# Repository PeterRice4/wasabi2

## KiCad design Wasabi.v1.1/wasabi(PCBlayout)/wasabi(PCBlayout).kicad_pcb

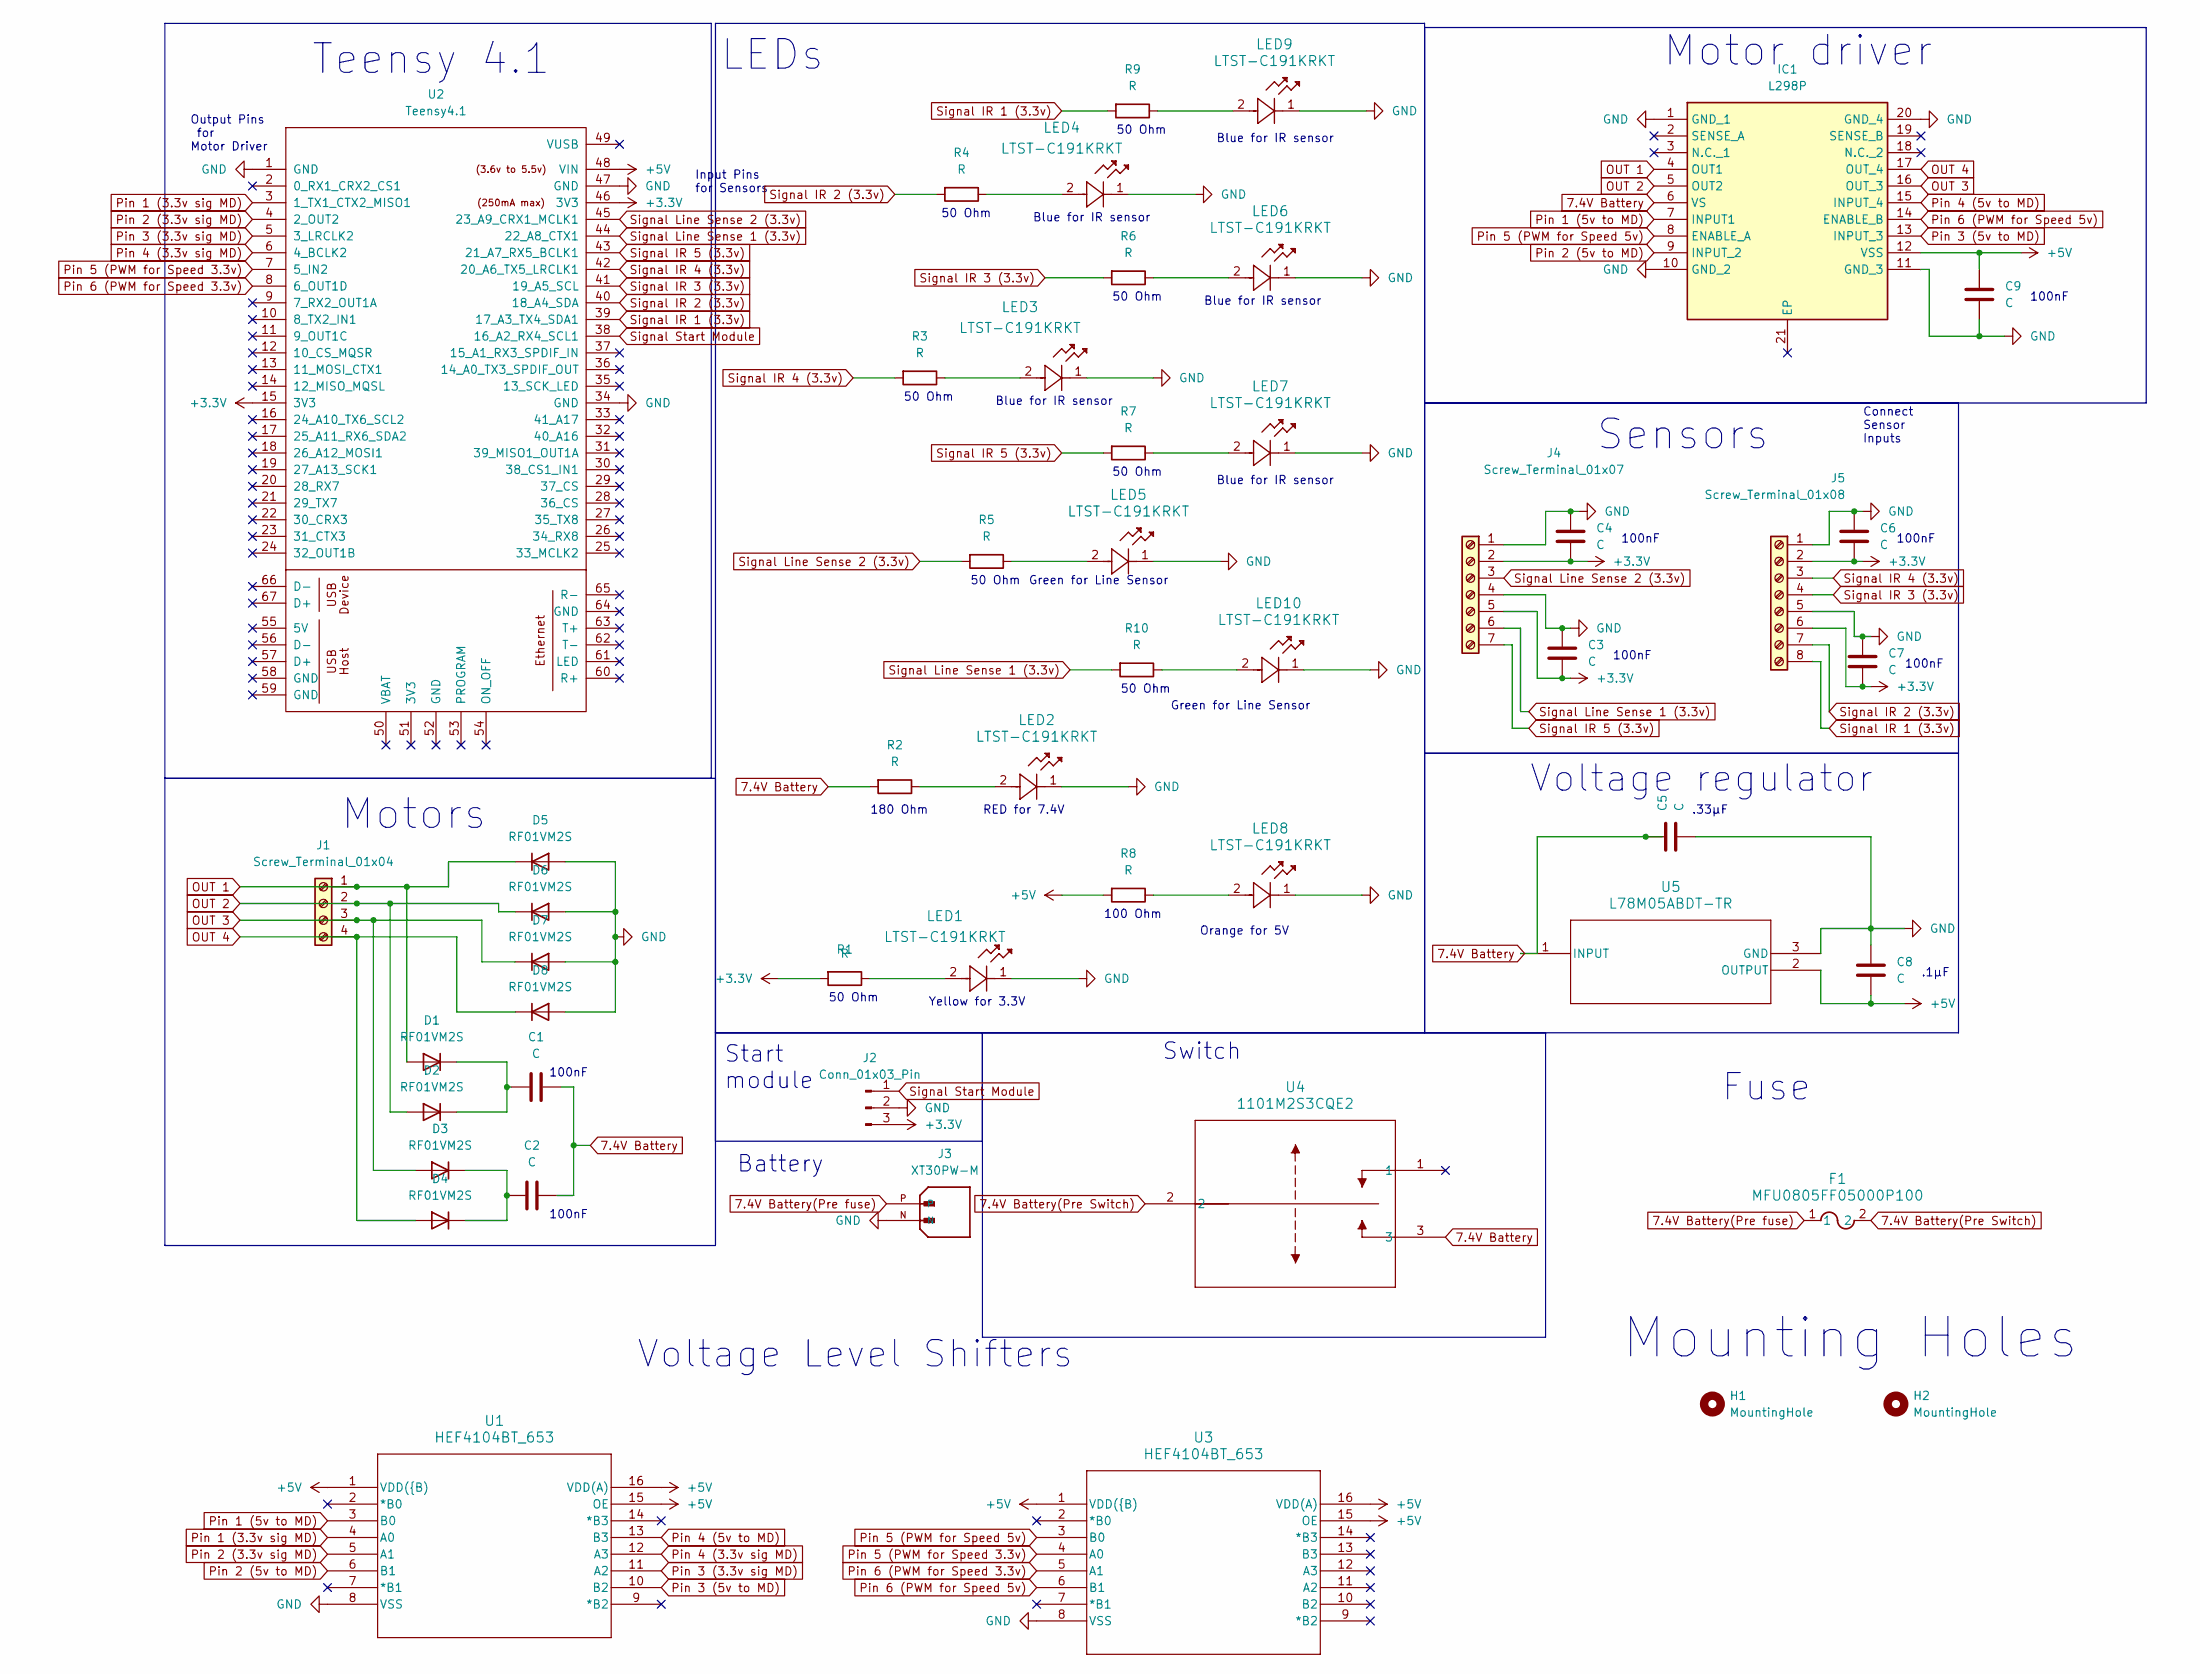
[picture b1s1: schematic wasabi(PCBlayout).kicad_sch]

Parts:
C1, C2, C3, C4, C6, C7, C8, C9: C; C_0402_1005Metric_Pad0.74x0.62mm_HandSolder
C5: C; C_0603_1608Metric_Pad1.08x0.95mm_HandSolder
D1, D2, D3, D4, D5, D6, D7, D8: RF01VM2S; D_SOD-123F
F1: MFU0805FF05000P100; MFU08055.00TR-ND(footprint)
H1, H2: MountingHole; MountingHole_2.2mm_M2_DIN965
IC1: L298P; L298p(footprint); Mouser Part Number 511-L298P
J1: Screw_Terminal_01x04; 4pinScrewTerminal(footprint)
J2: Conn_01x03_Pin; FanPinHeader_1x03_P2.54mm_Vertical
J3: XT30PW-M; AMASS_XT30PW-M(footprint); PARTREV 1.2
J4: Screw_Terminal_01x07; 7pinScrewTerminal(footprint)
J5: Screw_Terminal_01x08; 8pinScrewTerminal(footprint)
LED1, LED2, LED3, LED4, LED5, LED6, LED7, LED8, LED9, LED10: LTST-C191KRKT; LED_LTST-C191KRKT_LTO(footprint)
R1, R3, R4, R5, R6, R7, R9, R10: R; R_0603_1608Metric_Pad0.98x0.95mm_HandSolder
R2: R; R_1206_3216Metric_Pad1.30x1.75mm_HandSolder
R8: R; R_0805_2012Metric_Pad1.20x1.40mm_HandSolder
U1, U3: HEF4104BT_653; HEF4104BT,653(footprint)
U2: Teensy4.1; Teensy41 (footprint NEW)
U4: 1101M2S3CQE2; Switch1101M2S3CQE2(footprint)
U5: L78M05ABDT-TR; L78M05ABDT-TR(footprint)

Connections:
7.4V Battery: C1.2, C2.2, C5.1, IC1.6 (VS), R2.2, U4.3, U5.1 (INPUT)
7.4V Battery(Pre Switch): F1.2, U4.2
7.4V Battery(Pre fuse): F1.1, J3.P
+3.3V: C3.2, C4.2, C6.2, C7.2, J2.3, J4.2, J4.5, J5.2, J5.6, R1.2, U2.15 (3V3), U2.46 (3V3)
+5V: C8.2, C9.2, IC1.12 (VSS), R8.2, U1.1 (VDD({B)), U1.15 (OE), U1.16 (VDD(A)), U2.48 (VIN), U3.1 (VDD({B)), U3.15 (OE), U3.16 (VDD(A)), U5.2 (OUTPUT)
GND: C3.1, C4.1, C5.2, C6.1, C7.1, C8.1, C9.1, D5.2 (A), D6.2 (A), D7.2 (A), D8.2 (A), IC1.1 (GND_1), IC1.10 (GND_2), IC1.11 (GND_3), IC1.20 (GND_4), IC1.21 (EP), J2.2, J3.N, J4.1, J4.4, J5.1, J5.5, LED1.1, LED2.1, LED3.1, LED4.1, LED5.1, LED6.1, LED7.1, LED8.1, LED9.1, LED10.1, U1.8 (VSS), U2.1 (GND), U2.34 (GND), U2.47 (GND), U3.8 (VSS), U5.3 (GND)
unnamed: C1.1, D1.1 (K), D2.1 (K)
unnamed: C2.1, D3.1 (K), D4.1 (K)
unnamed: LED1.2, R1.1
unnamed: LED2.2, R2.1
unnamed: LED3.2, R3.1
unnamed: LED4.2, R4.1
unnamed: LED5.2, R5.1
unnamed: LED6.2, R6.1
unnamed: LED7.2, R7.1
unnamed: LED8.2, R8.1
unnamed: LED9.2, R9.1
unnamed: LED10.2, R10.1
OUT 1: D1.2 (A), D5.1 (K), IC1.4 (OUT1), J1.1
OUT 2: D2.2 (A), D6.1 (K), IC1.5 (OUT2), J1.2
OUT 3: D3.2 (A), D7.1 (K), IC1.16 (OUT_3), J1.3
OUT 4: D4.2 (A), D8.1 (K), IC1.17 (OUT_4), J1.4
Pin 1 (3.3v sig MD): U1.4 (A0), U2.3 (1_TX1_CTX2_MISO1)
Pin 1 (5v to MD): IC1.7 (INPUT1), U1.3 (B0)
Pin 2 (3.3v sig MD): U1.5 (A1), U2.4 (2_OUT2)
Pin 2 (5v to MD): IC1.9 (INPUT_2), U1.6 (B1)
Pin 3 (3.3v sig MD): U1.11 (A2), U2.5 (3_LRCLK2)
Pin 3 (5v to MD): IC1.13 (INPUT_3), U1.10 (B2)
Pin 4 (3.3v sig MD): U1.12 (A3), U2.6 (4_BCLK2)
Pin 4 (5v to MD): IC1.15 (INPUT_4), U1.13 (B3)
Pin 5 (PWM for Speed 3.3v): U2.7 (5_IN2), U3.4 (A0)
Pin 5 (PWM for Speed 5v): IC1.8 (ENABLE_A), U3.3 (B0)
Pin 6 (PWM for Speed 3.3v): U2.8 (6_OUT1D), U3.5 (A1)
Pin 6 (PWM for Speed 5v): IC1.14 (ENABLE_B), U3.6 (B1)
Signal IR 1 (3.3v): J5.8, R9.2, U2.39 (17_A3_TX4_SDA1)
Signal IR 2 (3.3v): J5.7, R4.2, U2.40 (18_A4_SDA)
Signal IR 3 (3.3v): J5.4, R6.2, U2.41 (19_A5_SCL)
Signal IR 4 (3.3v): J5.3, R3.2, U2.42 (20_A6_TX5_LRCLK1)
Signal IR 5 (3.3v): J4.7, R7.2, U2.43 (21_A7_RX5_BCLK1)
Signal Line Sense 1 (3.3v): J4.6, R10.2, U2.44 (22_A8_CTX1)
Signal Line Sense 2 (3.3v): J4.3, R5.2, U2.45 (23_A9_CRX1_MCLK1)
Signal Start Module: J2.1, U2.38 (16_A2_RX4_SCL1)

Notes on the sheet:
Voltage regulator
Blue for IR sensor
Start module
Mounting Holes
100nF
50 Ohm
Connect Sensor Inputs
Input Pins for Sensors
Fuse
Green for Line Sensor
LEDs
100 Ohm
Yellow for 3.3V
Motors
Teensy 4.1
Motor driver
Voltage Level Shifters
Battery
.1µF
180 Ohm
Output Pins for Motor Driver
Sensors
RED for 7.4V
Switch
Orange for 5V
.33µF

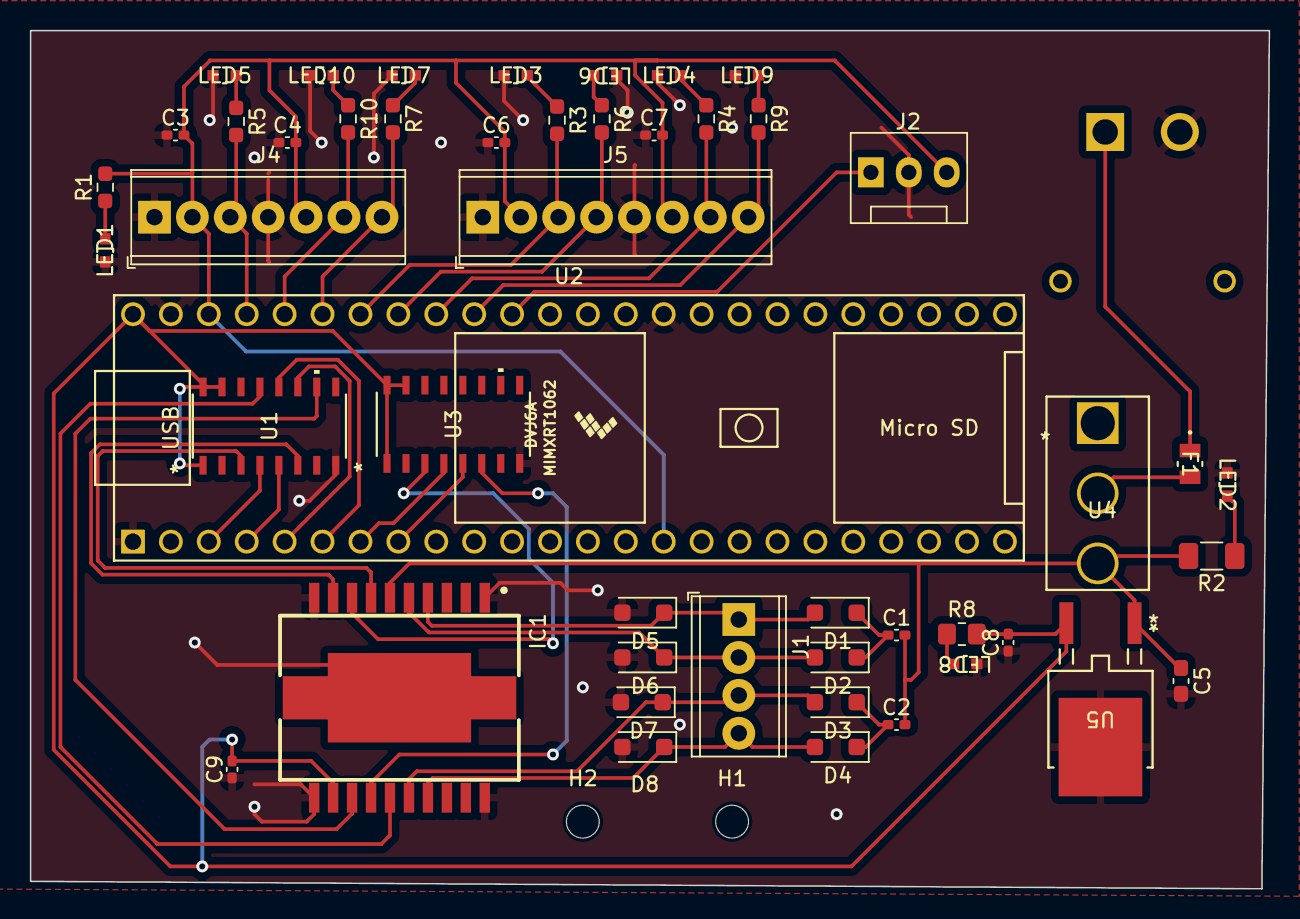
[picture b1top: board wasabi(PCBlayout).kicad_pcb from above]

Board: 2 copper layers, 83.0 x 57.5 mm, 51 parts (1 on the bottom side), 42 nets.

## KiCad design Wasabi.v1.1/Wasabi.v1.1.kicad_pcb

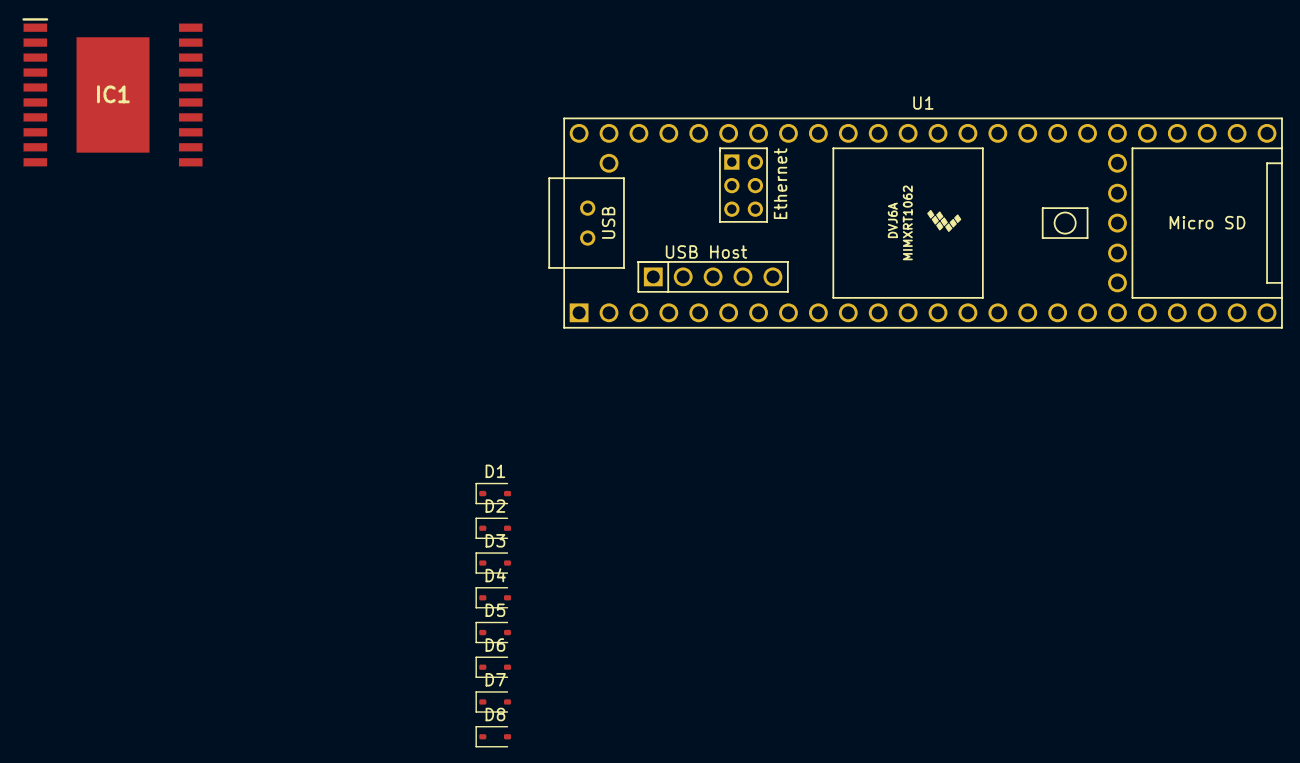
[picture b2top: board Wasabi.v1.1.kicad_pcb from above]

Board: 2 copper layers, 10 parts (0 on the bottom side), 11 nets, no tracks yet.

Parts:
D1, D2, D3, D4, D5, D6, D7, D8: RF01VM2S; D_SOD-323
IC1: L298P
U1: Teensy4.1; Teensy41

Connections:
GND: D1.2 (A), D2.2 (A), D3.2 (A), D4.2 (A), IC1.1 (GND_1), IC1.10 (GND_2), IC1.11 (GND_3), IC1.20 (GND_4), U1.1 (GND)
unnamed: D5.1 (K), D6.1 (K)
unnamed: D7.1 (K), D8.1 (K)
OUT 1: D1.1 (K), D5.2 (A), IC1.4 (OUT1)
OUT 2: D2.1 (K), D6.2 (A), IC1.5 (OUT2)
OUT 3: D3.1 (K), D7.2 (A), IC1.16 (OUT_3)
OUT 4: D4.1 (K), D8.2 (A), IC1.17 (OUT_4)
Pin 1: IC1.7 (INPUT1), U1.3 (1_TX1_CTX2_MISO1)
Pin 2: IC1.9 (INPUT_2), U1.4 (2_OUT2)
Pin 3: IC1.13 (INPUT_3), U1.5 (3_LRCLK2)
Pin 4: IC1.15 (INPUT_4), U1.6 (4_BCLK2)

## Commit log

2024-01-19 wasabi.v1.1 schematics
2024-01-19 Add CAD
2024-01-20 Revision 1
    - added blade
    - added 2x object sensors
2024-01-20 Revision 1.1
    - material changes
2024-01-26 Updated from 1/21
2024-01-26 organized things
2024-01-28 Wasabi 2.0
    smaller batte4ry
    smaller body
2024-02-04 Update Cad
2024-02-04 02/04/24
2024-02-05 Starting pcb layout
2024-02-05 02/05/24
2024-02-07 02/07/24
2024-02-09 02/08/24
2024-02-12 02/11/24
2024-02-12 02/12/24
2024-02-12 02/12/24 (1:23pm)
2024-02-12 final version (hopefully)
2024-02-18 back
2024-02-25 Wasabi 3.0
    probably finalized
2024-04-02 4/2/24
2024-04-05 revision 4
2024-04-17 4/17
2024-04-19 4/19
2024-06-09 Final CAD
2024-07-09 tolerance fix
2024-07-09 cleanup
2025-03-03 front plate
